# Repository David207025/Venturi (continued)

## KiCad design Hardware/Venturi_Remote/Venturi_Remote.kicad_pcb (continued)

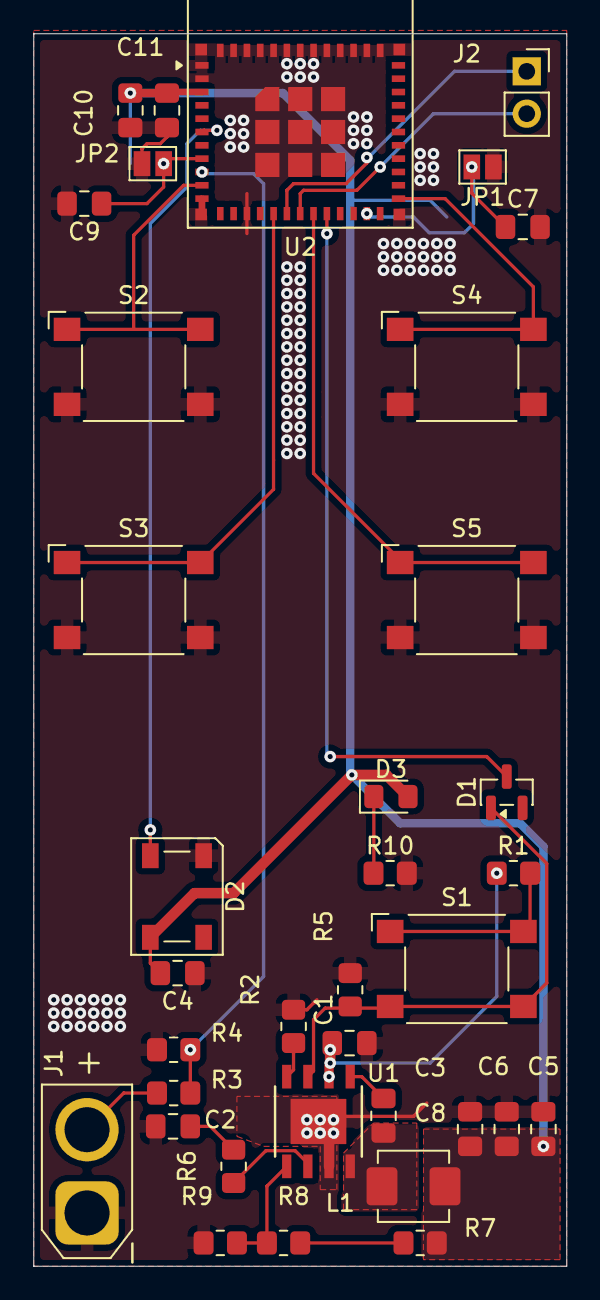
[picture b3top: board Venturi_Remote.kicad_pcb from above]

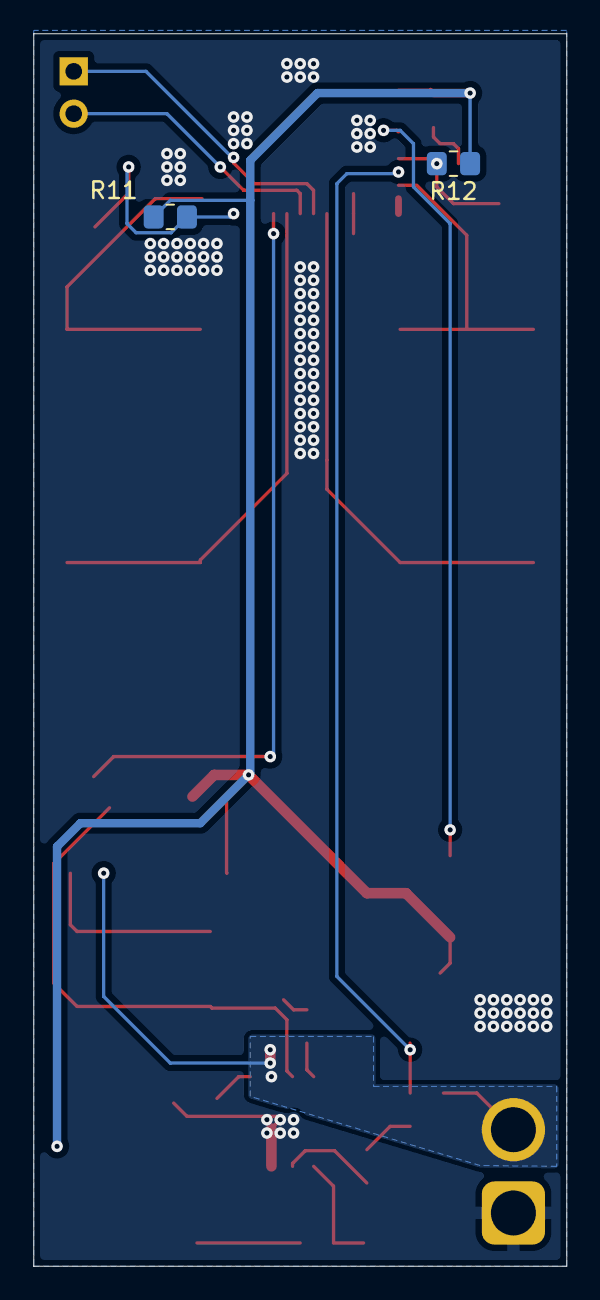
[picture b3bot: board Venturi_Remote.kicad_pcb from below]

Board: 2 copper layers, 32.0 x 74.0 mm, 38 parts (2 on the bottom side), 24 nets.

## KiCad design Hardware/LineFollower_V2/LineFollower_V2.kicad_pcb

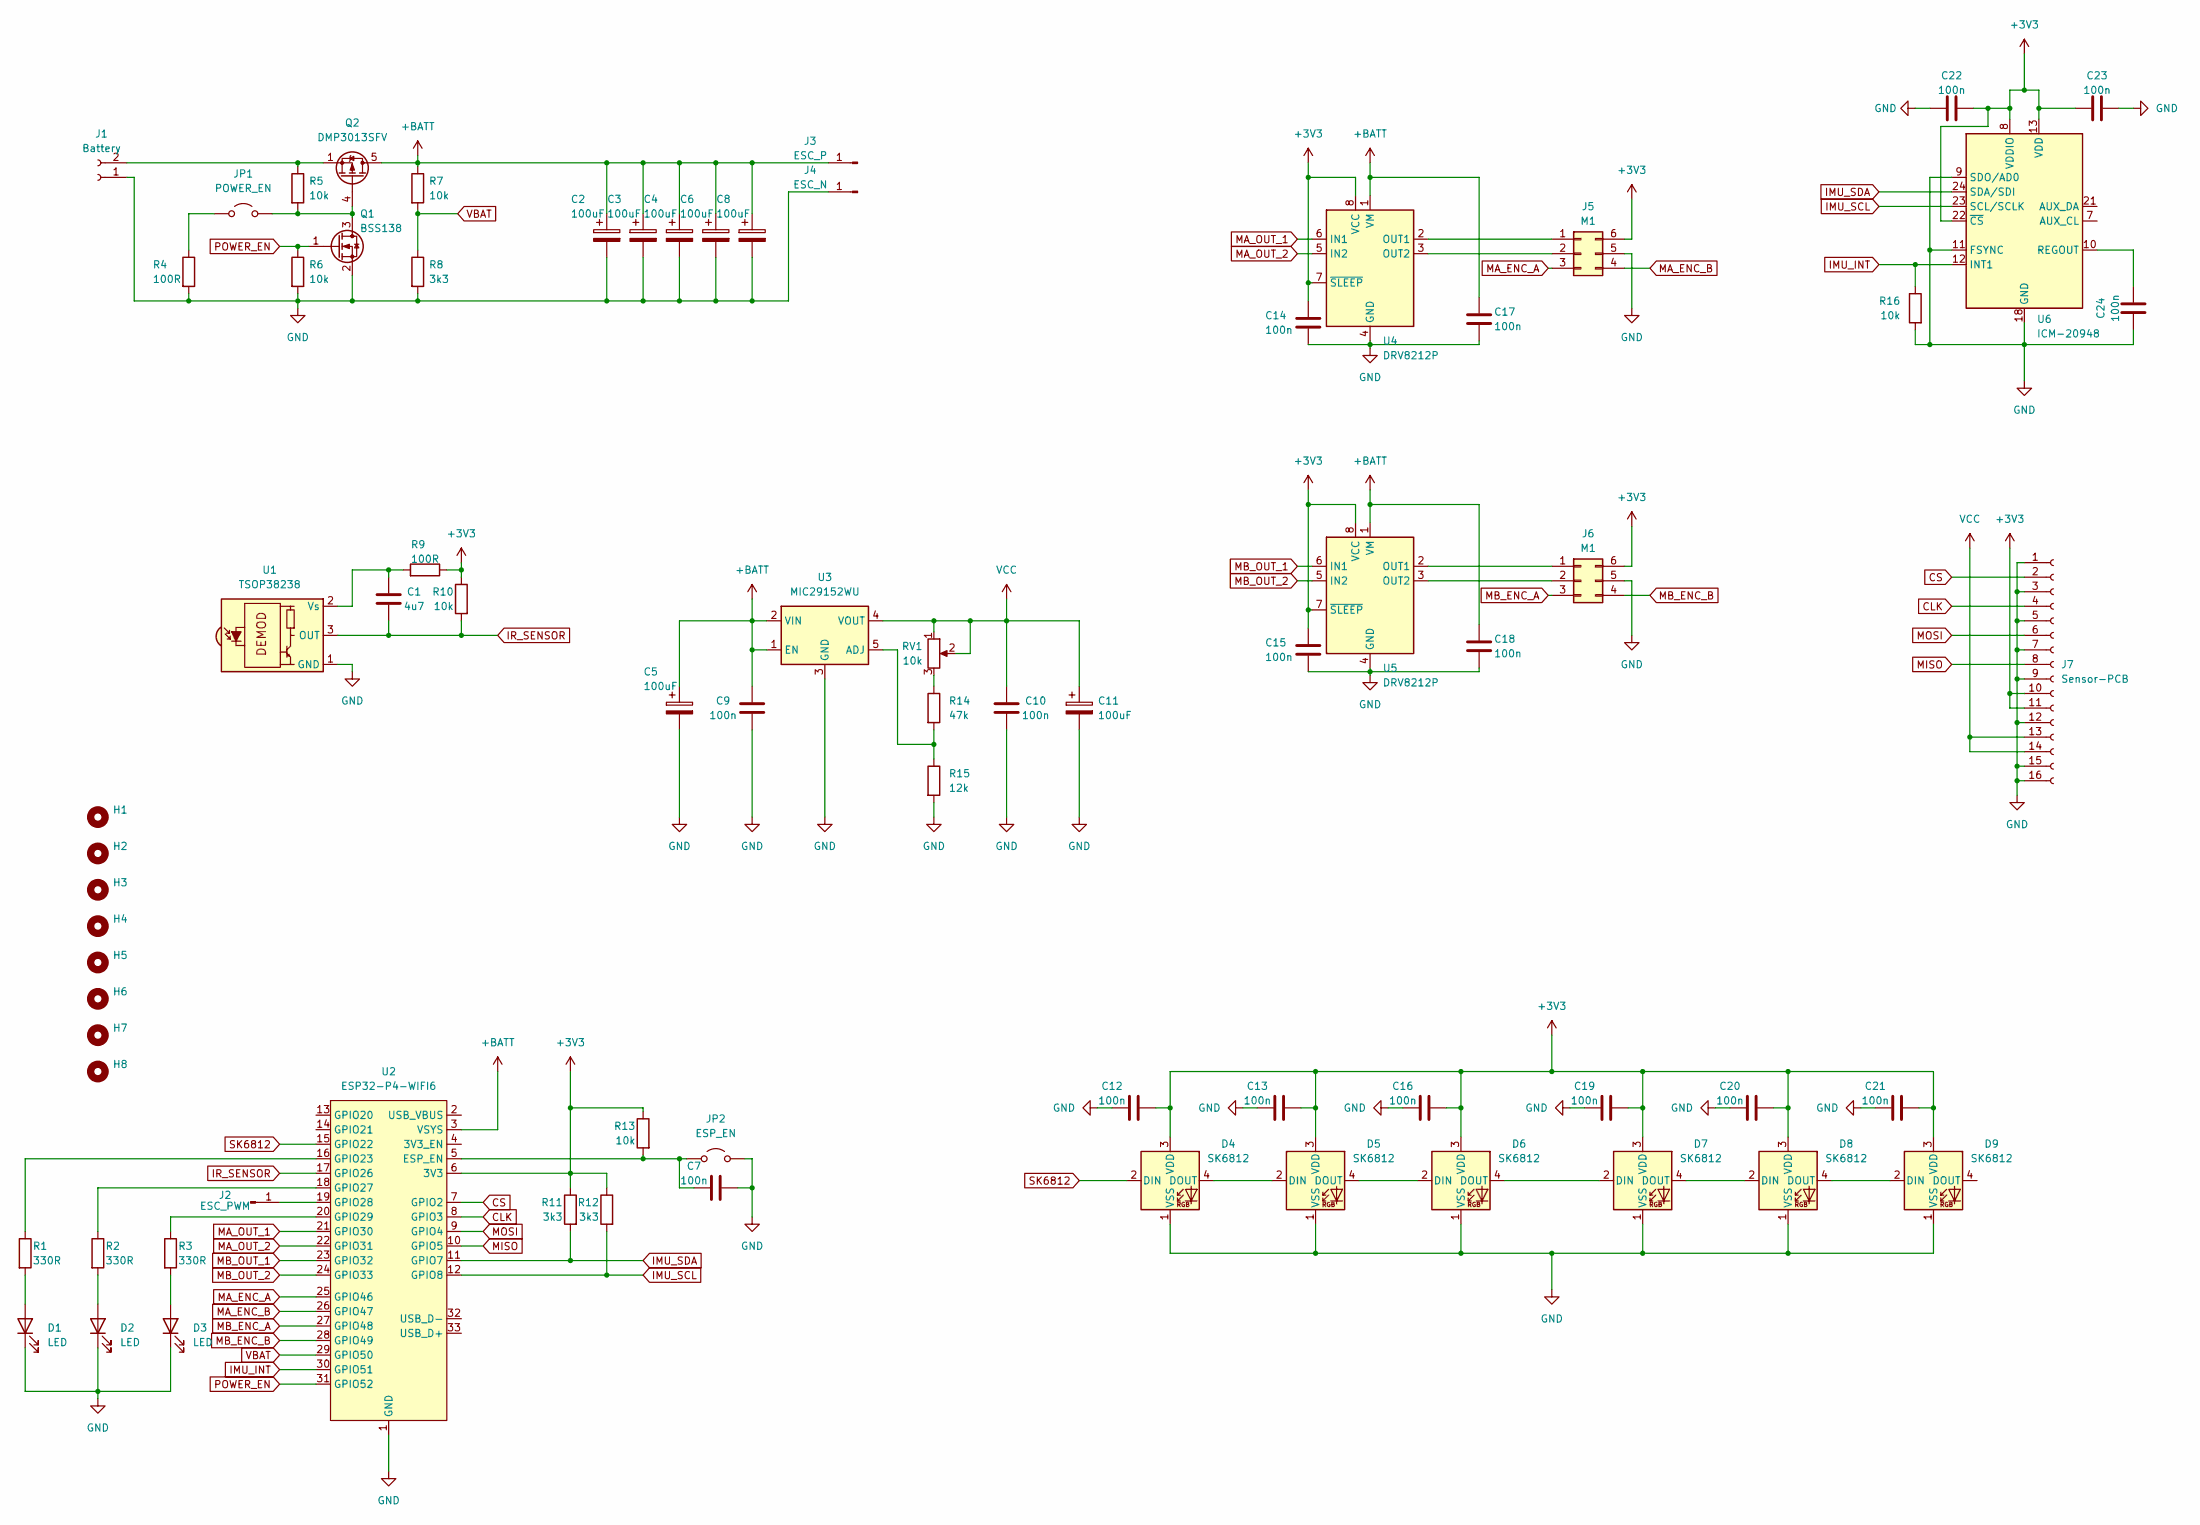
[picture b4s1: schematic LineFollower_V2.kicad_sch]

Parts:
C1: 4u7; C_0805_2012Metric_Pad1.18x1.45mm_HandSolder
C2, C3, C4, C5, C6, C8, C11: 100uF; CP_EIA-7343-15_Kemet-W_HandSolder
C7, C9, C10, C12, C13, C14, C15, C16, C17, C18, C19, C20, C21, C22, C23, C24: 100n; C_0805_2012Metric_Pad1.18x1.45mm_HandSolder
D1, D2, D3: LED; LED_0805_2012Metric_Pad1.15x1.40mm_HandSolder
D4, D5, D6, D7, D8, D9: SK6812; LED_SK6812_PLCC4_5.0x5.0mm_P3.2mm
H1, H2, H3, H4, H5, H6, H7, H8: MountingHole_3.2mm_M3_DIN965
J1: Battery; AMASS_XT30U-M_1x02_P5.0mm_Vertical
J2: ESC_PWM; SolderWire-0.25sqmm_1x01_D0.65mm_OD1.7mm
J3: ESC_P; SolderWire-0.25sqmm_1x01_D0.65mm_OD1.7mm
J4: ESC_N; SolderWire-0.25sqmm_1x01_D0.65mm_OD1.7mm
J5, J6: M1; PinHeader_2x03_P2.54mm_Vertical_SMD
J7: Sensor-PCB; SensorPCB-Connector
JP1: POWER_EN; TestPoint_2Pads_Pitch2.54mm_Drill0.8mm
JP2: ESP_EN; TestPoint_2Pads_Pitch2.54mm_Drill0.8mm
Q1: BSS138; SOT-23
Q2: DMP3013SFV; Diodes_PowerDI3333-8
R1, R2, R3: 330R; R_0805_2012Metric_Pad1.20x1.40mm_HandSolder
R4, R9: 100R; R_0805_2012Metric_Pad1.20x1.40mm_HandSolder
R5, R6, R7, R10, R13, R16: 10k; R_0805_2012Metric_Pad1.20x1.40mm_HandSolder
R8, R11, R12: 3k3; R_0805_2012Metric_Pad1.20x1.40mm_HandSolder
R14: 47k; R_0805_2012Metric_Pad1.20x1.40mm_HandSolder
R15: 12k; R_0805_2012Metric_Pad1.20x1.40mm_HandSolder
RV1: 10k; Potentiometer_Bourns_3314J_Vertical
U1: TSOP38238; Vishay_MINICAST-3Pin
U2: ESP32-P4-WIFI6
U3: MIC29152WU; TO-252-5_TabPin3
U4, U5: DRV8212P; WSON-8-1EP_2x2mm_P0.5mm_EP0.9x1.6mm_ThermalVias
U6: ICM-20948; InvenSense_QFN-24_3x3mm_P0.4mm

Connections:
+3V3: C12.2, C13.2, C14.1, C15.1, C16.2, C19.2, C20.2, C21.2, C22.1, C23.2, D4.3 (VDD), D5.3 (VDD), D6.3 (VDD), D7.3 (VDD), D8.3 (VDD), D9.3 (VDD), J5.6, J6.6, J7.10, J7.11, R9.1, R10.1, R11.1, R12.1, R13.1, U2.6 (3V3), U4.7 (~SLEEP), U4.8 (VCC), U5.7 (~SLEEP), U5.8 (VCC), U6.8 (VDDIO), U6.13 (VDD), U6.22 (~CS)
+BATT: C2.1, C3.1, C4.1, C5.1, C6.1, C8.1, C9.1, C17.1, C18.1, J3.1 (Pin_1_1), Q2.5 (D), R7.1, U2.3 (VSYS), U3.1 (EN), U3.2 (VIN), U4.1 (VM), U5.1 (VM)
CLK: J7.4, U2.8 (GPIO3)
CS: J7.2, U2.7 (GPIO2)
GND: C2.2, C3.2, C4.2, C5.2, C6.2, C7.2, C8.2, C9.2, C10.2, C11.2, C12.1, C13.1, C14.2, C15.2, C16.1, C17.2, C18.2, C19.1, C20.1, C21.1, C22.2, C23.1, C24.2, D1.1 (K), D2.1 (K), D3.1 (K), D4.1 (VSS), D5.1 (VSS), D6.1 (VSS), D7.1 (VSS), D8.1 (VSS), D9.1 (VSS), J1.1, J4.1 (Pin_1_1), J5.5, J6.5, J7.1, J7.3, J7.5, J7.7, J7.9, J7.12, J7.15, J7.16, JP2.2 (B), Q1.2 (S), R4.2, R6.2, R8.2, R15.2, R16.2, U1.1 (GND), U2.1 (GND), U3.3 (GND), U4.4 (GND), U4.9 (GND), U5.4 (GND), U5.9 (GND), U6.9 (SDO/AD0), U6.11 (FSYNC), U6.18 (GND), U6.20 (GND)
IMU_INT: R16.1, U2.30 (GPIO51), U6.12 (INT1)
IMU_SCL: R12.2, U2.12 (GPIO8), U6.23 (SCL/SCLK)
IMU_SDA: R11.2, U2.11 (GPIO7), U6.24 (SDA/SDI)
IR_SENSOR: C1.1, R10.2, U1.3 (OUT), U2.17 (GPIO26)
MA_ENC_A: J5.3, U2.25 (GPIO46)
MA_ENC_B: J5.4, U2.26 (GPIO47)
MA_OUT_1: U2.21 (GPIO30), U4.6 (IN1)
MA_OUT_2: U2.22 (GPIO31), U4.5 (IN2)
MB_ENC_A: J6.3, U2.27 (GPIO48)
MB_ENC_B: J6.4, U2.28 (GPIO49)
MB_OUT_1: U2.23 (GPIO32), U5.6 (IN1)
MB_OUT_2: U2.24 (GPIO33), U5.5 (IN2)
MISO: J7.8, U2.10 (GPIO5)
MOSI: J7.6, U2.9 (GPIO4)
unnamed: D1.2 (A), R1.2
unnamed: D2.2 (A), R2.2
unnamed: D3.2 (A), R3.2
unnamed: D4.4 (DOUT), D5.2 (DIN)
unnamed: D5.4 (DOUT), D6.2 (DIN)
unnamed: D6.4 (DOUT), D7.2 (DIN)
unnamed: D7.4 (DOUT), D8.2 (DIN)
unnamed: D8.4 (DOUT), D9.2 (DIN)
unnamed: J1.2, Q2.1 (S), Q2.2 (S), Q2.3 (S), R5.1
unnamed: J2.1 (Pin_1_1), U2.19 (GPIO28)
unnamed: J5.1, U4.2 (OUT1)
unnamed: J5.2, U4.3 (OUT2)
unnamed: J6.1, U5.2 (OUT1)
unnamed: J6.2, U5.3 (OUT2)
unnamed: JP1.1 (A), R4.1
unnamed: JP1.2 (B), Q1.3 (D), Q2.4 (G), R5.2
unnamed: C7.1, JP2.1 (A), R13.2, U2.5 (ESP_EN)
unnamed: R14.1, RV1.3
unnamed: C1.2, R9.2, U1.2 (Vs)
unnamed: R1.1, U2.16 (GPIO23)
unnamed: R2.1, U2.18 (GPIO27)
unnamed: R3.1, U2.20 (GPIO29)
unnamed: R14.2, R15.1, U3.5 (ADJ)
unnamed: C24.1, U6.10 (REGOUT)
POWER_EN: Q1.1 (G), R6.1, U2.31 (GPIO52)
SK6812: D4.2 (DIN), U2.15 (GPIO22)
VBAT: R7.2, R8.1, U2.29 (GPIO50)
VCC: C10.1, C11.1, J7.13, J7.14, RV1.1, RV1.2, U3.4 (VOUT)

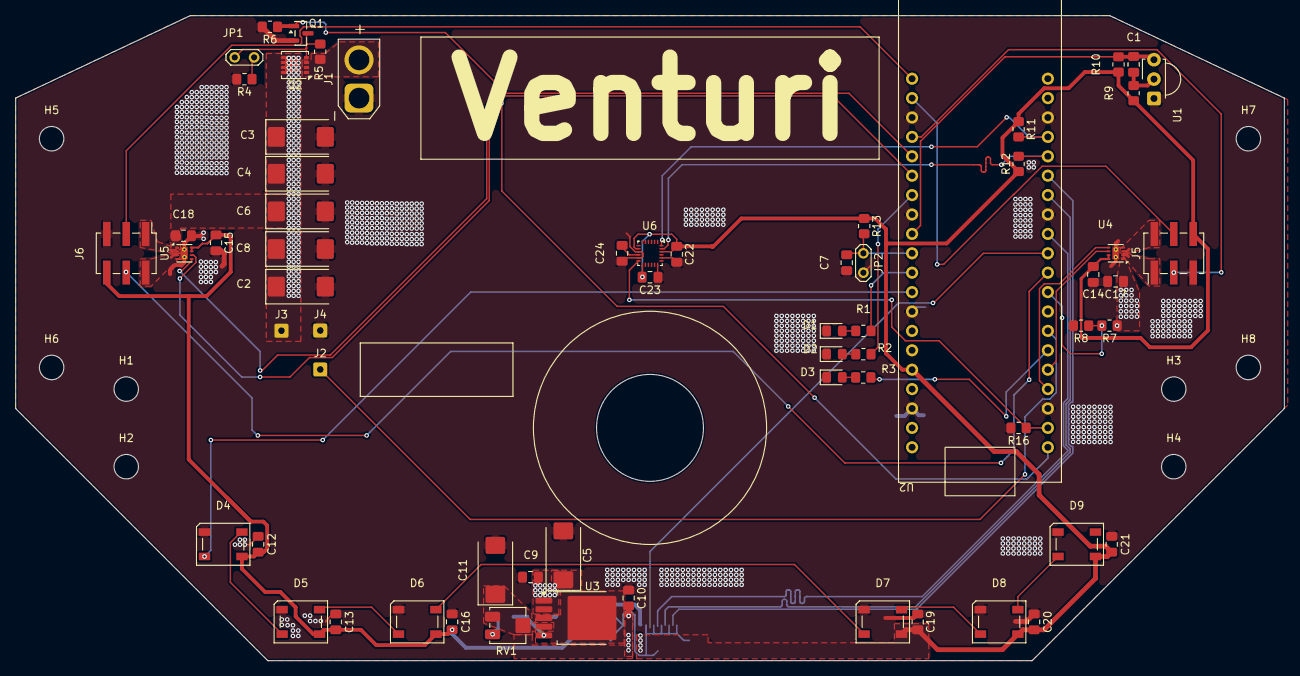
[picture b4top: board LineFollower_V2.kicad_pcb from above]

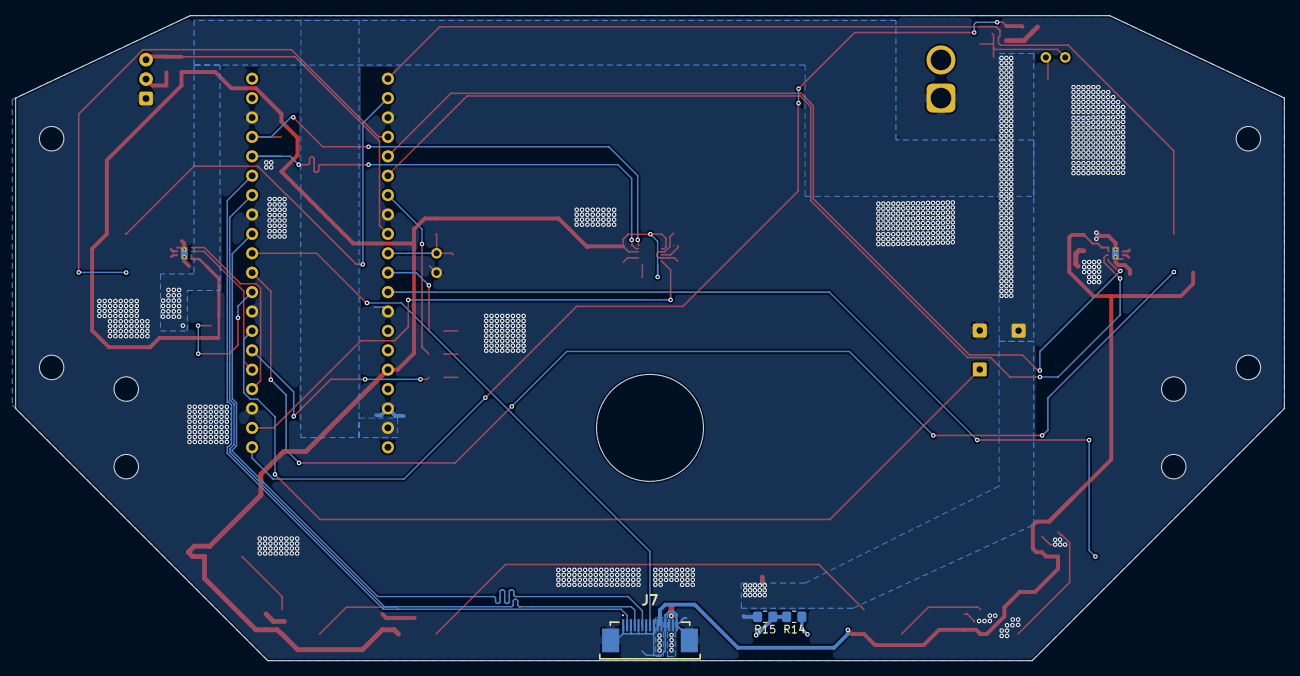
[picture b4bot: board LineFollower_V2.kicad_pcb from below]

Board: 2 copper layers, 166.1 x 84.5 mm, 75 parts (3 on the bottom side), 47 nets.

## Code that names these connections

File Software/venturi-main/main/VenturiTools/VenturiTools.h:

#ifndef VENTURITOOLS_H
#define VENTURITOOLS_H

#include <stdio.h>
#include <string.h>
#include "esp_err.h"
#include "esp_log.h"
#include "driver/uart.h"
#include "driver/gpio.h"
#include "driver/spi_master.h"
#include "driver/temperature_sensor.h"
#include "driver/touch_sens.h"
#include "esp_vfs_fat.h"
#include "sdmmc_cmd.h"
#include "soc/spi_struct.h"
#include "soc/gpio_struct.h"
#include "VenturiEngine/VenturiEngine.h"

#define UART_PORT     UART_NUM_1
#define TX_PIN        18
#define RX_PIN        19
#define UART_BUF_SIZE 2048

#define PIN_TM        16
#define PIN_UDPR      17

#define PIN_ADC_CS    2
#define PIN_ADC_CLK   3
#define PIN_ADC_MOSI  4
#define PIN_ADC_MISO  5

#define PIN_IMU_CS    23
#define PIN_IMU_CLK   22
#define PIN_IMU_MOSI  21
#define PIN_IMU_MISO  20
#define PIN_IMU_INT   51

class VenturiTools {
private:
    int debugLevel;
    temperature_sensor_handle_t tempHandle;
    bool temperatureSensorAvailable;

    spi_device_handle_t spi_imu;
    spi_device_handle_t spi_adc;

    sdmmc_card_t *card;
    bool sdCardMounted;

    static TaskHandle_t taskToNotify;
    static volatile bool s_touchFlags[16];
    static volatile bool s_fingerOnPad[16];


    touch_sensor_handle_t global_touch_controller;
    // Native Touch structures
    touch_channel_handle_t touchHandle[15];

    static bool touch_filter_cb(touch_sensor_handle_t handle, const touch_active_event_data_t *event_data,
                                          void *user_ctx);

    void initSD();

public:
    char* jsonBuffer;
    static portMUX_TYPE bufferMutex;

    static volatile TelemetryFrame frameA, frameB;
    static volatile TelemetryFrame* activeWriteFrame;
    static volatile TelemetryFrame* activeReadFrame;

    spi_dev_t *_spi_imu_hw;
    spi_dev_t *_spi_adc_hw;

    VenturiTools(int debug_level = 0);

    ~VenturiTools();

    static void initUART(int baudRate, int txPin, int rxPin, const char *configJson);

    static void sendFrame(const TelemetryFrame *frame);

    void initSPI();

    void initFastHardwarePipeline();

    void performFastSPIRead(uint8_t *adc_buf, uint8_t *imu_buf);

    void setTaskNotificationHandle(TaskHandle_t taskHandle);

    void initTouchChannel(uint8_t pin, uint16_t threshold);

    void initTouchChannelInterrupt(uint8_t pin);

    bool isChannelTouched(uint8_t pin);

    FILE *openFile(const char *filename, const char *mode);

    void reloadSD();

    float getTemperature();
};

#endif // VENTURITOOLS_H

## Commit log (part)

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2026-05-26 Folder structure setup
2026-05-26 Removed old backups from LineFollower_V2
2026-05-26 Removed backup files from LineFollower_V2
2026-05-26 Removed backup files for LineFollower Sensor PCB
2026-05-26 Refactor hardware directories and update gitignore
2026-05-26 Remove .DS_Store files
2026-05-26 Added BLE Diagnostics code and ESP32 PlatformIO Project
2026-06-03 Added asynchronous SPI reads
2026-06-04 Updated PCB-Design for 20MHz SPI speed
2026-06-11 Updated PCB and schematic files. Removed read-lock from Venturi-Main
2026-06-13 Switched to pure ESP-IDF for the ESP32-P4. Added custom firmware for the onboard ESP32-C6
2026-06-13 Implemented 50ms update loop, removed MicroLink submodule and added debug pads to all SPI lanes on the main PCB
